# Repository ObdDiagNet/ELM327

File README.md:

ELM327 adapter and firmware based on PIC18F25K80
==========================================

<p><b>You are always wanted to built ELM327 adapter but firmware was not available? Not anymore! Everything is here.</b>
This was a side project done for testing ELM327 firmware available openly on GitHub. I just wanted to see if it works. And yes, it is pretty much functional! When the original ELM327 based on PIC18F2480, this one is built around PIC18F25K80 chip. From the schematic prospective it is almost the same, the only difference is VCAP/VDDCORE decoupling capacitor C11 on pin 6.</p>

<p>J1850 voltage regulator is simplified based on the fact that the logical voltage level is 3.3V vs. 5V for PIC18F2480. The adapter uses 9-pin D type female connector to link up to vehicle's OBD-II J1962 connector. The pinout is De-facto a standard for OBD cables. The cable available on eBay or AliExpress from many vendors. The printed circuit board layout is in Eagle 9 format.</p>

### Simplified schematic and improved firmware
One of many additional features of PIC18F25K80 is analog comparator. The previous schematic has comparator-like functionality with transistors Q4 and Q5. It can be replaced with PIC built-in analog comparator, see below. It should improve the reliability J1850 PWM signal handling. The firmware was modified as well to enable the internal comparator (the second in archive). Some unused pins turned to outputs, like RA3 and RC2. Using ULN2003 can reduce the number of external components. The Chinese knock-offs of ULN2003 are quite inexpensive. Another solution here to minimize number of components - using resistor arrays.

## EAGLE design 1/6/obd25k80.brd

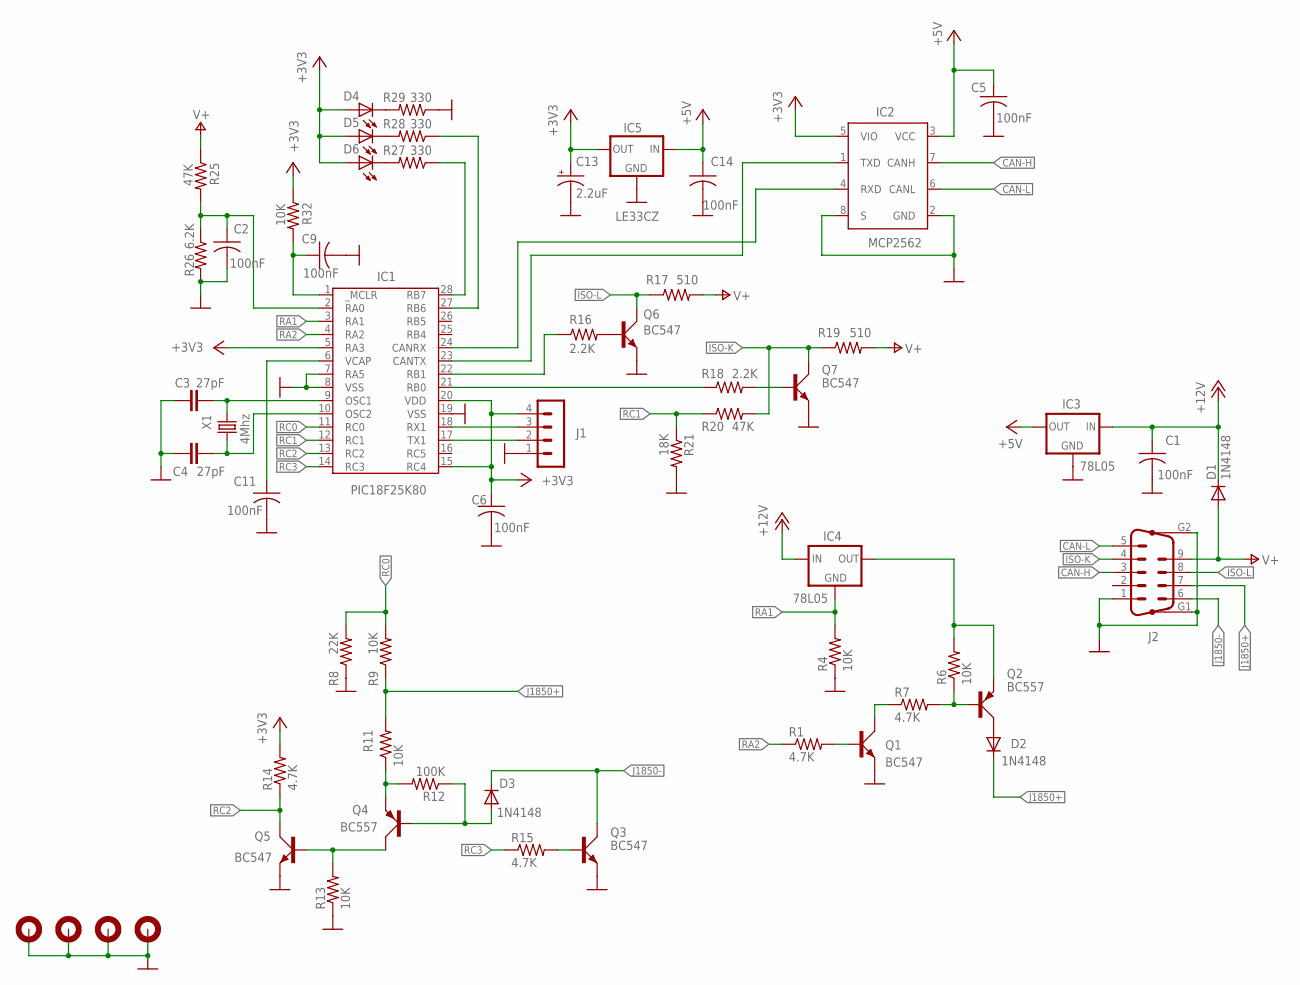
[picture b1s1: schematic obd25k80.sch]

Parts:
C1, C2, C5, C6, C9, C11, C14: 100nF; C050-025X075
C3, C4: 27pF; C2.5-2
C13: 2.2uF; E2,5-5
D1, D2, D3: 1N4148; D035-10M
D4, D5, D6: LED5MM
H1, H2, H3, H4: MOUNT-PAD-ROUND2.8; 2,8-PAD
IC1: PIC18F25K80; DIL28
IC2: MCP2562; DIL8
IC3, IC4: 78L05; 78LXX
IC5: LE33CZ; 78LXX
J1: MA04-1
J2: DB9-M; M09HP
Q1, Q3, Q5, Q6, Q7: BC547; SOT54A
Q2, Q4: BC557; SOT54A
R1, R7, R14, R15: 4.7K; 0207/10
R4, R6, R9, R11, R13, R32: 10K; 0207/10
R8: 22K; 0207/10
R12: 100K; 0207/10
R16, R18: 2.2K; 0207/10
R17, R19: 510; 0207/10
R20, R25: 47K; 0207/10
R21: 18K; 0207/10
R26: 6.2K; 0207/10
R27, R28, R29: 330; 0207/10
X1: 4Mhz; HC49/S

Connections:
+3V3: C6.1, C13.+, D4.A, D5.A, D6.A, IC1.5 (RA3), IC1.15 (RC4), IC1.20 (VDD), IC2.5 (VIO), IC5.OUT, J1.4, R14.2, R32.1
+5V: C5.1, C14.1, IC2.3 (VCC), IC3.OUT, IC5.IN
+12V: C1.1, D1.C, IC3.IN, IC4.IN
CAN-H: IC2.7 (CANH), J2.3
CAN-L: IC2.6 (CANL), J2.5
GND: C1.2, C2.2, C3.1, C4.2, C5.2, C6.2, C9.2, C11.2, C13.-, C14.2, H1.B2,8, H2.B2,8, H3.B2,8, H4.B2,8, IC1.7 (RA5), IC1.8 (VSS), IC1.19 (VSS), IC2.2 (GND), IC2.8 (S), IC3.GND, IC5.GND, J1.1, J2.1, J2.G1, J2.G2, Q1.E, Q3.E, Q5.E, Q6.E, Q7.E, R4.1, R8.1, R13.1, R21.2, R26.2, R29.1
ISO-K: J2.4, Q7.C, R19.1, R20.2
ISO-L: J2.8, Q6.C, R17.1
J1850+: D2.C, J2.7, R9.1, R11.2
J1850-: D3.C, J2.6, Q3.C
unnamed: D4.K (C), R29.2
unnamed: IC1.28 (RB7), R27.1
unnamed: D5.K (C), R28.2
unnamed: C9.1, IC1.1 (_MCLR), R32.2
unnamed: IC1.22 (RB1), R16.1
unnamed: D6.K (C), R27.2
unnamed: IC1.27 (RB6), R28.1
unnamed: C11.1, IC1.6 (VCAP)
unnamed: Q6.B, R16.2
unnamed: IC1.18 (RX1), J1.3
unnamed: IC1.24 (CANRX), IC2.4 (RXD)
unnamed: IC1.17 (TX1), J1.2
unnamed: IC1.21 (RB0), R18.1
unnamed: C3.2, IC1.9 (OSC1), X1.2
unnamed: Q3.B, R15.2
unnamed: IC1.23 (CANTX), IC2.1 (TXD)
unnamed: Q7.B, R18.2
unnamed: Q1.C, R7.1
unnamed: C2.1, IC1.2 (RA0), R25.2, R26.1
unnamed: Q1.B, R1.2
unnamed: Q2.B, R6.1, R7.2
unnamed: IC4.OUT, Q2.E, R6.2
unnamed: D2.A, Q2.C
unnamed: Q4.E, R11.1, R12.2
unnamed: D3.A, Q4.B, R12.1
unnamed: Q4.C, Q5.B, R13.2
unnamed: C4.1, IC1.10 (OSC2), X1.1
RA1: IC1.3 (RA1), IC4.GND, R4.2
RA2: IC1.4 (RA2), R1.1
RC0: IC1.11 (RC0), R8.2, R9.2
RC1: IC1.12 (RC1), R20.1, R21.1
RC2: IC1.13 (RC2), Q5.C, R14.1
RC3: IC1.14 (RC3), R15.1
V+: D1.A, J2.9, R17.2, R19.2, R25.1

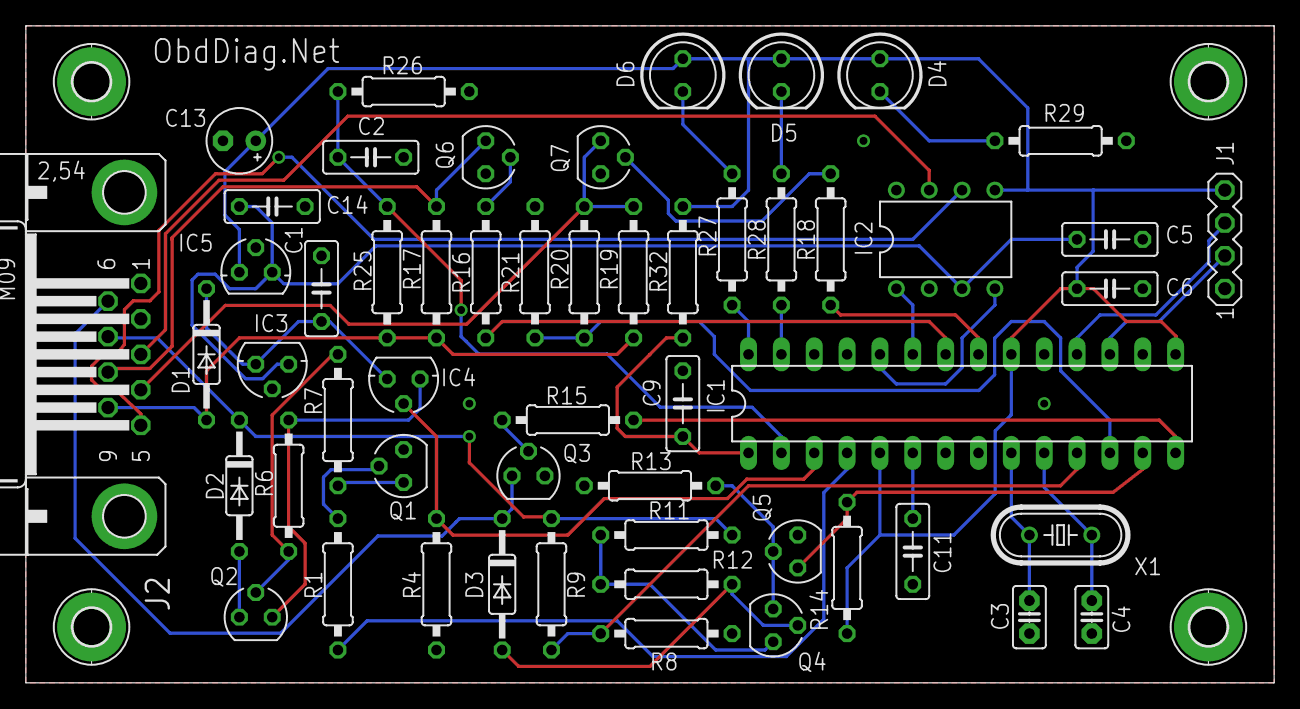
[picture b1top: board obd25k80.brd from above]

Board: 2 copper layers, 96.5 x 50.8 mm, 58 parts (0 on the bottom side), 44 nets.

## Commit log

2024-09-22 Initial release
2024-09-22 More..
2024-09-22 Added picture
2024-09-22 More...
2024-09-22 Added description
2024-09-22 Minor changes
2024-09-22 Minor changes (2)
2024-09-22 Cleanup
2024-09-22 Added firmware
